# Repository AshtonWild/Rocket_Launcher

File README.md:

# Rocket Launcher

Open hardware for a hobby model-rocket system built around two ESP32 boards:

| Board | What it does | Size | Version |
|---|---|---|---|
| [Rocket V1 flight computer](docs/rocket-v1.md) | Flies in the rocket. Drives four canard servos, reads an IMU and logs to microSD. | 70 × 50 mm, 2 layers | V1 |
| [Ground Station V1 launch controller](docs/ground-station-v1.md) | Stays at the pad. Arms and fires the igniter, checks continuity, and reads GPS, compass and barometer. | 100 × 70 mm, 2 layers | V1 |

Both boards are through-hole only, so they can be hand-soldered, and both use a socketed 30-pin ESP32 DevKit V1. They talk to each other before launch over a 3-wire serial umbilical.

Designed by **Ashton W** in KiCad 10.

| Rocket V1 | Ground Station V1 |
|---|---|
|  |  |

## Safety

The Ground Station switches a 12 V battery into a pyrotechnic igniter. Treat it as live whenever the igniter battery is connected.

- Fit the **SAFE shunt** (J6) whenever you are near the rocket. It shorts the igniter leads together.
- Pull the **ARM plug** (J3) and remove the **key** before approaching the pad.
- The red **ARMED** LED is wired directly to the armed 12 V line. If it is lit, the firing circuit has power, whatever the ESP32 is doing.
- The continuity check passes about 13 µA through the igniter. With the SAFE shunt fitted it reads "connected" whether or not an igniter is attached.
- Follow your national model-rocketry safety code and local law. This design is provided as-is, with no warranty; you are responsible for how you build and use it.

## Documentation

| Document | What it covers |
|---|---|
| [User manual](docs/user-manual.md) | Assembly, bench tests, installation and the launch-day procedure |
| [How it works](docs/how-it-works.md) | Circuit-by-circuit technical description of both boards |
| [Rocket V1](docs/rocket-v1.md) | Connectors, ESP32 pins, test points and known issues |
| [Ground Station V1](docs/ground-station-v1.md) | Firing circuit, connectors, ESP32 pins and known issues |
| [Manufacturing](docs/manufacturing.md) | Ordering the boards from JLCPCB |
| [Changelog](CHANGELOG.md) | What is in this release |

## Repository layout

```
Rocket_V1/           KiCad project: flight computer
Ground_Station_V1/   KiCad project: launch controller
lib/                 Shared ESP32 DevKit symbol and footprint
docs/                Board documentation, schematic PDFs, board renders
  rocket-v1.md
  ground-station-v1.md
  user-manual.md
  how-it-works.md
  manufacturing.md
  schematics/        Schematic PDF and SVG for each board
  images/            Board renders and a prototype photo
*/JLCPCB/            Ready-to-order Gerber zip and parts list for each board
CHANGELOG.md         What is in this release
```

## Opening the projects

1. Install [KiCad 10](https://www.kicad.org/download/) or newer.
2. Open `Rocket_V1/Rocket_V1.kicad_pro` or `Ground_Station_V1/Ground_Station_V1.kicad_pro`.

The ESP32 DevKit symbol and footprint load from `lib/` through a relative path, so the folders must stay side by side as they are here. Every other part comes from KiCad's standard libraries.

Don't want to install KiCad? The schematics are in [docs/schematics](docs/schematics) as PDFs.

## Ordering boards

Each project has a `JLCPCB` folder holding a Gerber zip you can upload as-is, the individual Gerber files, and a parts list. Settings and pre-order checks are in [docs/manufacturing.md](docs/manufacturing.md).

## Status

Both boards pass KiCad's electrical and design rule checks with no errors. **Neither revision has been manufactured or tested yet.** Read the "Known issues" section of each board's page before ordering.

Firmware is not part of this repository. Each board page lists the ESP32 pin assignments needed to write it.

## License

Designed by Ashton W. No license has been chosen yet, so all rights are reserved by default. Add a `LICENSE` file before inviting others to reuse the design. CERN-OHL-P and CC BY-SA are common choices for open hardware.

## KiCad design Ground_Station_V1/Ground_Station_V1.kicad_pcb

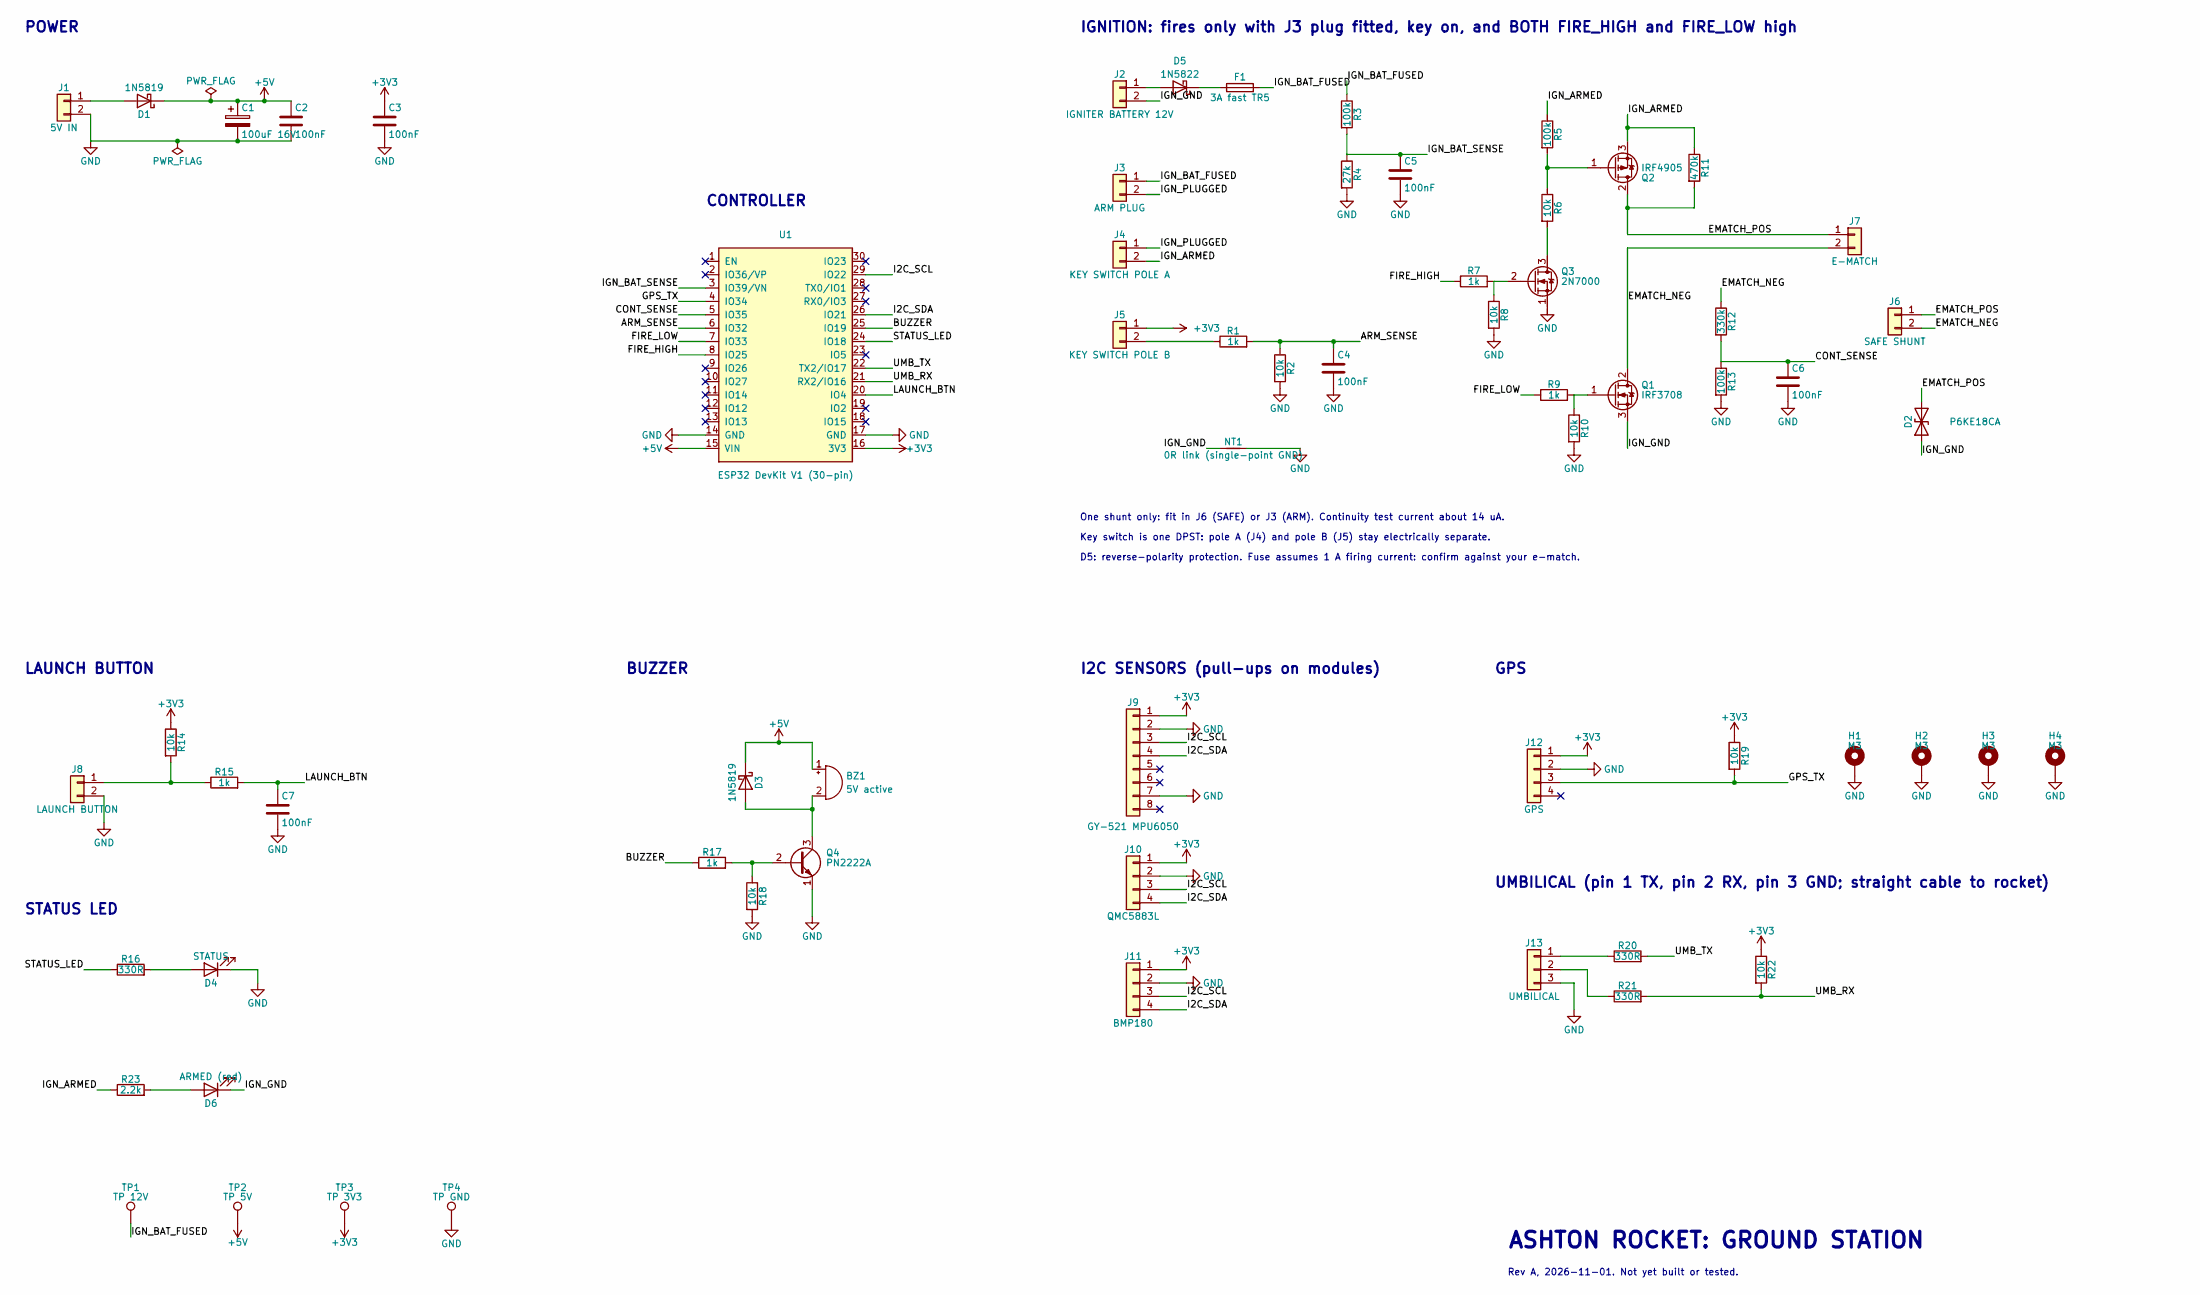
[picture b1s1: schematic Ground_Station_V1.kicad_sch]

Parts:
BZ1: 5V active; Buzzer_12x9.5RM7.6
C1: 100uF 16V; CP_Radial_D6.3mm_P2.50mm
C2, C3, C4, C5, C6, C7: 100nF; C_Disc_D3.0mm_W2.0mm_P2.50mm
D1, D3: 1N5819; D_DO-41_SOD81_P7.62mm_Horizontal
D2: P6KE18CA; D_DO-15_P10.16mm_Horizontal
D4: STATUS; LED_D3.0mm
D5: 1N5822; D_DO-201AD_P12.70mm_Horizontal
D6: ARMED (red); LED_D3.0mm
F1: 3A fast TR5; Fuse_Littelfuse_372_D8.50mm
H1, H2, H3, H4: M3; MountingHole_3.2mm_M3_DIN965_Pad
J1: 5V IN; TerminalBlock_Phoenix_MKDS-1,5-2-5.08_1x02_P5.08mm_Horizont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
J2: IGNITER BATTERY 12V; TerminalBlock_Phoenix_MKDS-1,5-2-5.08_1x02_P5.08mm_Horizont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
J3: ARM PLUG; PinHeader_1x02_P2.54mm_Vertical
J4: KEY SWITCH POLE A; TerminalBlock_Phoenix_MKDS-1,5-2-5.08_1x02_P5.08mm_Horizont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
J5: KEY SWITCH POLE B; PinHeader_1x02_P2.54mm_Vertical
J6: SAFE SHUNT; PinHeader_1x02_P2.54mm_Vertical
J7: E-MATCH; TerminalBlock_Phoenix_MKDS-1,5-2-5.08_1x02_P5.08mm_Horizont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
J8: LAUNCH BUTTON; PinHeader_1x02_P2.54mm_Vertical
J9: GY-521 MPU6050; PinHeader_1x08_P2.54mm_Vertical
J10: QMC5883L; PinHeader_1x04_P2.54mm_Vertical
J11: BMP180; PinHeader_1x04_P2.54mm_Vertical
J12: GPS; PinHeader_1x04_P2.54mm_Vertical
J13: UMBILICAL; PinHeader_1x03_P2.54mm_Vertical
NT1: 0R link (single-point GND); R_Axial_DIN0207_L6.3mm_D2.5mm_P7.62mm_Horizontal
Q1: IRF3708; TO-220-3_Vertical
Q2: IRF4905; TO-220-3_Vertical
Q3: 2N7000; TO-92_Inline
Q4: PN2222A; TO-92_Inline
R1, R7, R9, R15, R17: 1k; R_Axial_DIN0207_L6.3mm_D2.5mm_P7.62mm_Horizontal
R2, R6, R8, R10, R14, R18, R19, R22: 10k; R_Axial_DIN0207_L6.3mm_D2.5mm_P7.62mm_Horizontal
R3, R5, R13: 100k; R_Axial_DIN0207_L6.3mm_D2.5mm_P7.62mm_Horizontal
R4: 27k; R_Axial_DIN0207_L6.3mm_D2.5mm_P7.62mm_Horizontal
R11: 470k; R_Axial_DIN0207_L6.3mm_D2.5mm_P7.62mm_Horizontal
R12: 330k; R_Axial_DIN0207_L6.3mm_D2.5mm_P7.62mm_Horizontal
R16, R20, R21: 330R; R_Axial_DIN0207_L6.3mm_D2.5mm_P7.62mm_Horizontal
R23: 2.2k; R_Axial_DIN0207_L6.3mm_D2.5mm_P7.62mm_Horizontal
TP1: TP 12V; TestPoint_Keystone_5000-5004_Miniature
TP2: TP 5V; TestPoint_Keystone_5000-5004_Miniature
TP3: TP 3V3; TestPoint_Keystone_5000-5004_Miniature
TP4: TP GND; TestPoint_Keystone_5000-5004_Miniature
U1: ESP32 DevKit V1 (30-pin); ESP32_DevKit_V1_30pin_Socket

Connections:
+3V3: C3.1, J5.1, J9.1, J10.1, J11.1, J12.1, R14.1, R19.1, R22.1, TP3.1, U1.16 (3V3)
+5V: BZ1.1 (+), C1.1, C2.1, D1.1 (K), D3.1 (K), TP2.1, U1.15 (VIN)
/ARM_SENSE: C4.1, R1.2, R2.1, U1.6 (IO32)
/BUZZER: R17.1, U1.25 (IO19)
/CONT_SENSE: C6.1, R12.2, R13.1, U1.5 (IO35)
/EMATCH_NEG: J6.2, J7.2, Q1.2 (D), R12.1
/EMATCH_POS: D2.2 (A2), J6.1, J7.1, Q2.2 (D), R11.2
/FIRE_HIGH: R7.1, U1.8 (IO25)
/FIRE_LOW: R9.1, U1.7 (IO33)
/GPS_TX: J12.3, R19.2, U1.4 (IO34)
/I2C_SCL: J9.3, J10.3, J11.3, U1.29 (IO22)
/I2C_SDA: J9.4, J10.4, J11.4, U1.26 (IO21)
/IGN_ARMED: J4.2, Q2.3 (S), R5.1, R11.1, R23.1
/IGN_BAT_FUSED: F1.2, J3.1, R3.1, TP1.1
/IGN_BAT_SENSE: C5.1, R3.2, R4.1, U1.3 (IO39/VN)
/IGN_GND: D2.1 (A1), D6.1 (K), J2.2, NT1.1, Q1.3 (S)
/IGN_PLUGGED: J3.2, J4.1
/LAUNCH_BTN: C7.1, R15.2, U1.20 (IO4)
/STATUS_LED: R16.1, U1.24 (IO18)
/UMB_RX: R21.2, R22.2, U1.21 (RX2/IO16)
/UMB_TX: R20.2, U1.22 (TX2/IO17)
GND: C1.2, C2.2, C3.2, C4.2, C5.2, C6.2, C7.2, D4.1 (K), H1.1, H2.1, H3.1, H4.1, J1.2, J8.2, J9.2, J9.7, J10.2, J11.2, J12.2, J13.3, NT1.2, Q3.1 (S), Q4.1 (E), R2.2, R4.2, R8.2, R10.2, R13.2, R18.2, TP4.1, U1.14 (GND), U1.17 (GND)
unnamed: BZ1.2 (-), D3.2 (A), Q4.3 (C)
unnamed: D1.2 (A), J1.1
unnamed: D4.2 (A), R16.2
unnamed: D5.2 (A), J2.1
unnamed: D5.1 (K), F1.1
unnamed: D6.2 (A), R23.2
unnamed: J5.2, R1.1
unnamed: J8.1, R14.2, R15.1
unnamed: J13.1, R20.1
unnamed: J13.2, R21.1
unnamed: Q1.1 (G), R9.2, R10.1
unnamed: Q2.1 (G), R5.2, R6.1
unnamed: Q3.3 (D), R6.2
unnamed: Q3.2 (G), R7.2, R8.1
unnamed: Q4.2 (B), R17.2, R18.1

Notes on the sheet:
POWER
CONTROLLER
IGNITION: fires only with J3 plug fitted, key on, and BOTH FIRE_HIGH and FIRE_LOW high
LAUNCH BUTTON
STATUS LED
BUZZER
I2C SENSORS (pull-ups on modules)
GPS
UMBILICAL (pin 1 TX, pin 2 RX, pin 3 GND; straight cable to rocket)
One shunt only: fit in J6 (SAFE) or J3 (ARM). Continuity test current about 14 uA.
Key switch is one DPST: pole A (J4) and pole B (J5) stay electrically separate.
ASHTON ROCKET: GROUND STATION
Rev A, 2026-11-01. Not yet built or tested.
D5: reverse-polarity protection. Fuse assumes 1 A firing current: confirm against your e-match.

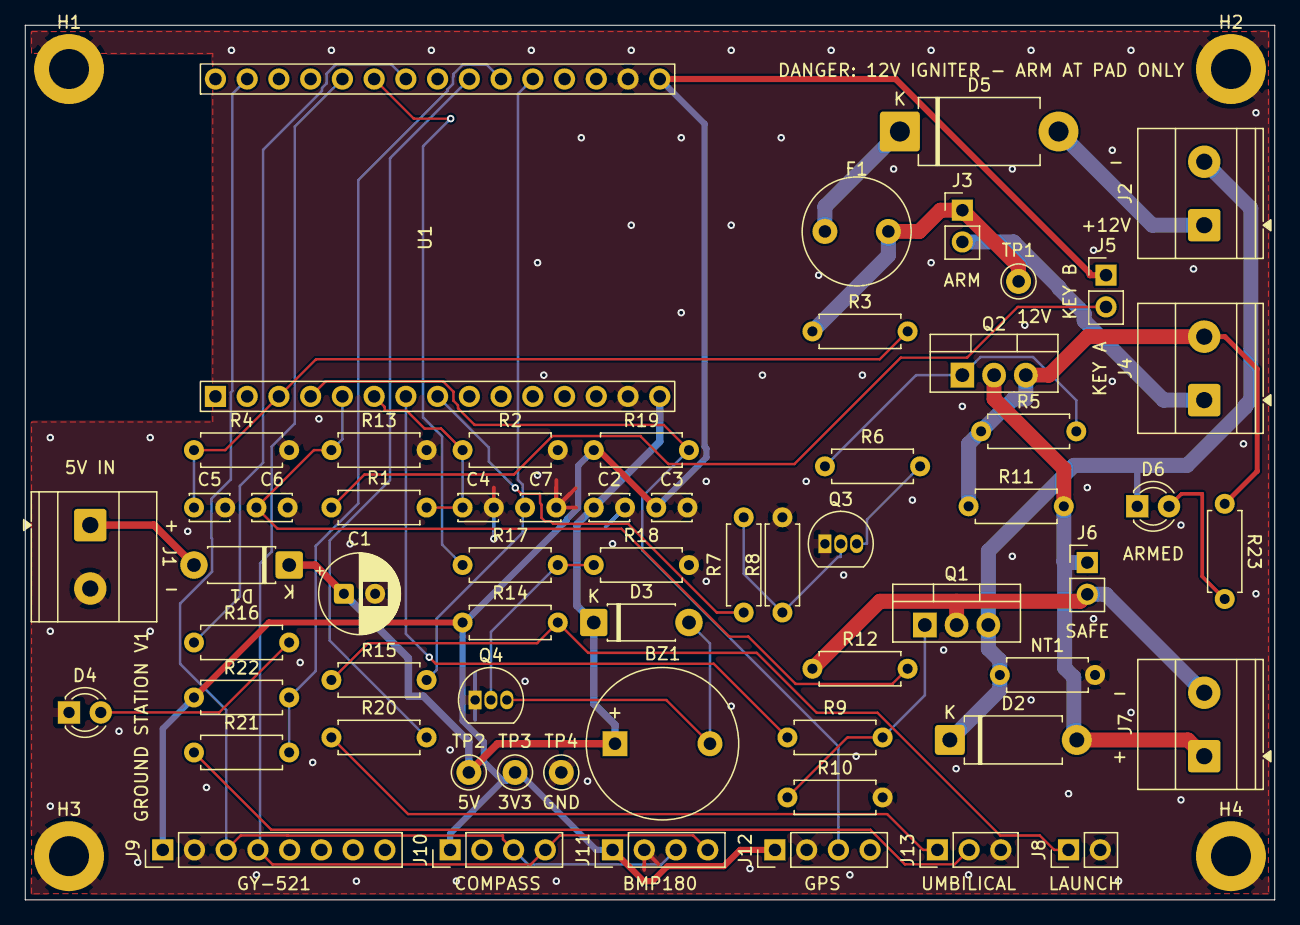
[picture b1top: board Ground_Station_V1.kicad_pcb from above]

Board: 2 copper layers, 100.0 x 70.0 mm, 65 parts (0 on the bottom side), 37 nets.

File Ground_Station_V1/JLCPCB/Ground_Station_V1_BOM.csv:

"Reference","Value","Footprint","QUANTITY"
"BZ1","5V active","Buzzer_Beeper:Buzzer_12x9.5RM7.6","1"
"C1","100uF 16V","Capacitor_THT:CP_Radial_D6.3mm_P2.50mm","1"
"C2-C7","100nF","Capacitor_THT:C_Disc_D3.0mm_W2.0mm_P2.50mm","6"
"D1,D3","1N5819","Diode_THT:D_DO-41_SOD81_P7.62mm_Horizontal","2"
"D2","P6KE18CA","Diode_THT:D_DO-15_P10.16mm_Horizontal","1"
"D4","STATUS","LED_THT:LED_D3.0mm","1"
"D5","1N5822","Diode_THT:D_DO-201AD_P12.70mm_Horizontal","1"
"D6","ARMED (red)","LED_THT:LED_D3.0mm","1"
"F1","3A fast TR5","Fuse:Fuse_Littelfuse_372_D8.50mm","1"
"H1-H4","M3","MountingHole:MountingHole_3.2mm_M3_DIN965_Pad","4"
"J1","5V IN","TerminalBlock_Phoenix:TerminalBlock_Phoenix_MKDS-1,5-2-5.08_1x02_P5.08mm_Horizontal","1"
"J2","IGNITER BATTERY 12V","TerminalBlock_Phoenix:TerminalBlock_Phoenix_MKDS-1,5-2-5.08_1x02_P5.08mm_Horizontal","1"
"J3","ARM PLUG","Connector_PinHeader_2.54mm:PinHeader_1x02_P2.54mm_Vertical","1"
"J4","KEY SWITCH POLE A","TerminalBlock_Phoenix:TerminalBlock_Phoenix_MKDS-1,5-2-5.08_1x02_P5.08mm_Horizontal","1"
"J5","KEY SWITCH POLE B","Connector_PinHeader_2.54mm:PinHeader_1x02_P2.54mm_Vertical","1"
"J6","SAFE SHUNT","Connector_PinHeader_2.54mm:PinHeader_1x02_P2.54mm_Vertical","1"
"J7","E-MATCH","TerminalBlock_Phoenix:TerminalBlock_Phoenix_MKDS-1,5-2-5.08_1x02_P5.08mm_Horizontal","1"
"J8","LAUNCH BUTTON","Connector_PinHeader_2.54mm:PinHeader_1x02_P2.54mm_Vertical","1"
"J9","GY-521 MPU6050","Connector_PinHeader_2.54mm:PinHeader_1x08_P2.54mm_Vertical","1"
"J10","QMC5883L","Connector_PinHeader_2.54mm:PinHeader_1x04_P2.54mm_Vertical","1"
"J11","BMP180","Connector_PinHeader_2.54mm:PinHeader_1x04_P2.54mm_Vertical","1"
"J12","GPS","Connector_PinHeader_2.54mm:PinHeader_1x04_P2.54mm_Vertical","1"
"J13","UMBILICAL","Connector_PinHeader_2.54mm:PinHeader_1x03_P2.54mm_Vertical","1"
"NT1","0R link (single-point GND)","Resistor_THT:R_Axial_DIN0207_L6.3mm_D2.5mm_P7.62mm_Horizontal","1"
"Q1","IRF3708","Package_TO_SOT_THT:TO-220-3_Vertical","1"
"Q2","IRF4905","Package_TO_SOT_THT:TO-220-3_Vertical","1"
"Q3","2N7000","Package_TO_SOT_THT:TO-92_Inline","1"
"Q4","PN2222A","Package_TO_SOT_THT:TO-92_Inline","1"
"R1,R7,R9,R15,R17","1k","Resistor_THT:R_Axial_DIN0207_L6.3mm_D2.5mm_P7.62mm_Horizontal","5"
"R2,R6,R8,R10,R14,R18,R19,R22","10k","Resistor_THT:R_Axial_DIN0207_L6.3mm_D2.5mm_P7.62mm_Horizontal","8"
"R3,R5,R13","100k","Resistor_THT:R_Axial_DIN0207_L6.3mm_D2.5mm_P7.62mm_Horizontal","3"
"R4","27k","Resistor_THT:R_Axial_DIN0207_L6.3mm_D2.5mm_P7.62mm_Horizontal","1"
"R11","470k","Resistor_THT:R_Axial_DIN0207_L6.3mm_D2.5mm_P7.62mm_Horizontal","1"
"R12","330k","Resistor_THT:R_Axial_DIN0207_L6.3mm_D2.5mm_P7.62mm_Horizontal","1"
"R16,R20,R21","330R","Resistor_THT:R_Axial_DIN0207_L6.3mm_D2.5mm_P7.62mm_Horizontal","3"
"R23","2.2k","Resistor_THT:R_Axial_DIN0207_L6.3mm_D2.5mm_P7.62mm_Horizontal","1"
"TP1","TP 12V","TestPoint:TestPoint_Keystone_5000-5004_Miniature","1"
"TP2","TP 5V","TestPoint:TestPoint_Keystone_5000-5004_Miniature","1"
"TP3","TP 3V3","TestPoint:TestPoint_Keystone_5000-5004_Miniature","1"
"TP4","TP GND","TestPoint:TestPoint_Keystone_5000-5004_Miniature","1"
"U1","ESP32 DevKit V1 (30-pin)","ESP32_DevKit:ESP32_DevKit_V1_30pin_Socket","1"

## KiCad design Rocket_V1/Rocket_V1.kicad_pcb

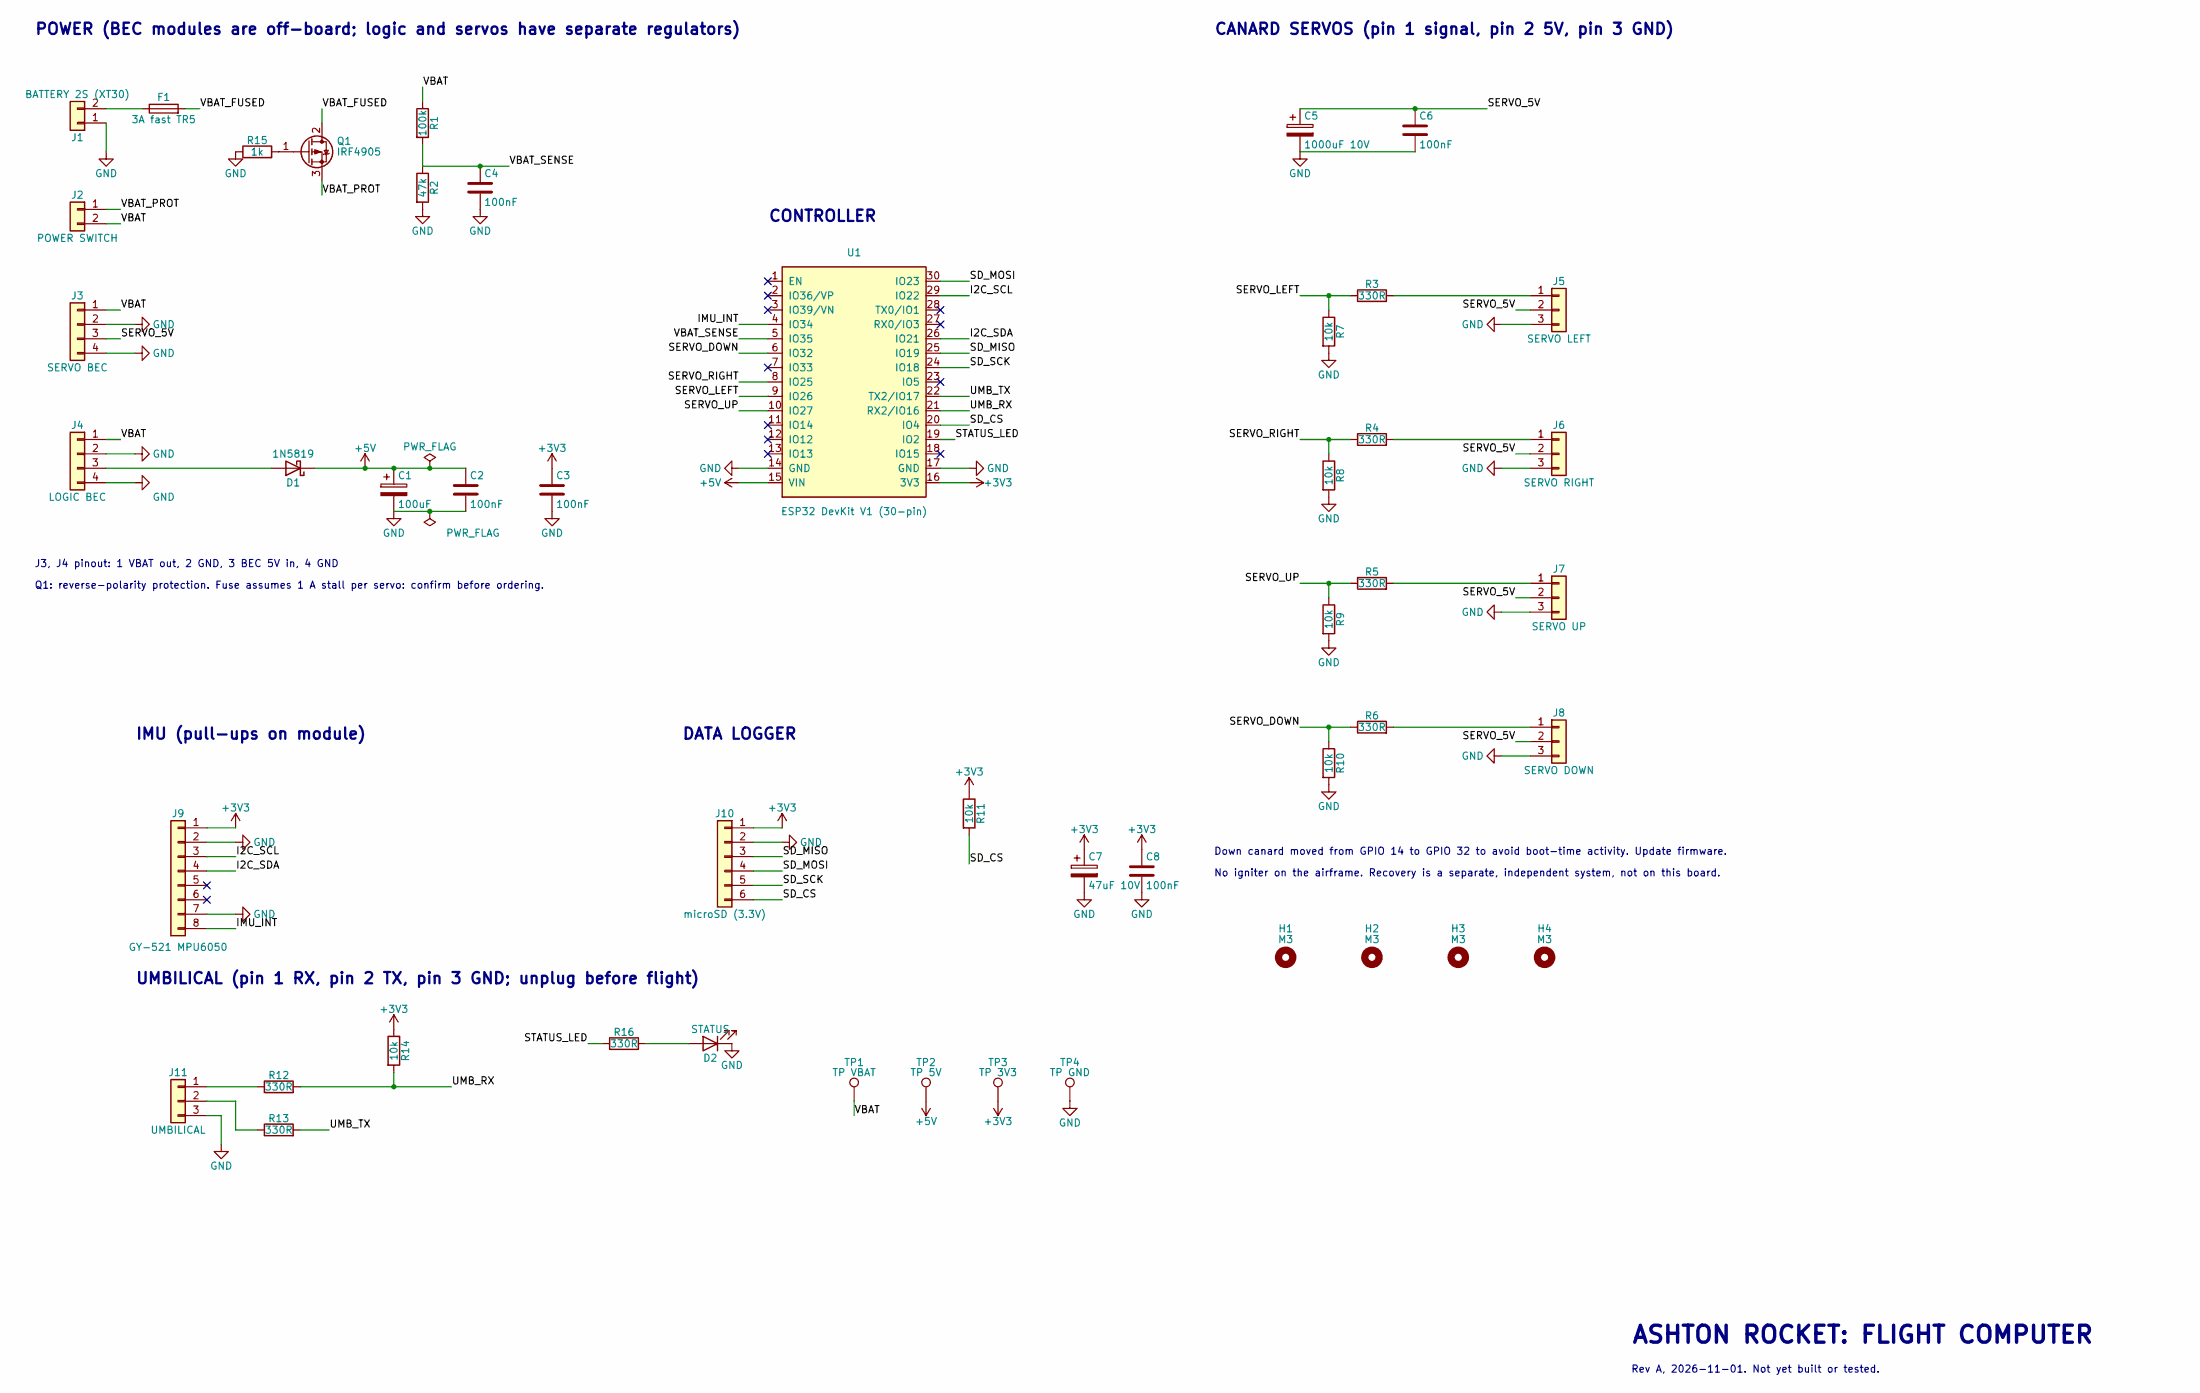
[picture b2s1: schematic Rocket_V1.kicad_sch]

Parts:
C1: 100uF; CP_Radial_D6.3mm_P2.50mm; Voltage 16V
C2, C3, C4, C6, C8: 100nF; C_Disc_D3.0mm_W2.0mm_P2.50mm
C5: 1000uF 10V; CP_Radial_D10.0mm_P5.00mm
C7: 47uF 10V; CP_Radial_D5.0mm_P2.50mm
D1: 1N5819; D_DO-41_SOD81_P7.62mm_Horizontal
D2: STATUS; LED_D3.0mm
F1: 3A fast TR5; Fuse_Littelfuse_372_D8.50mm; Voltage 32V min
H1, H2, H3, H4: M3; MountingHole_3.2mm_M3
J1: BATTERY 2S (XT30); AMASS_XT30U-M_1x02_P5.0mm_Vertical
J2: POWER SWITCH; PinHeader_1x02_P2.54mm_Vertical
J3: SERVO BEC; PinHeader_1x04_P2.54mm_Vertical
J4: LOGIC BEC; PinHeader_1x04_P2.54mm_Vertical
J5: SERVO LEFT; PinHeader_1x03_P2.54mm_Vertical
J6: SERVO RIGHT; PinHeader_1x03_P2.54mm_Vertical
J7: SERVO UP; PinHeader_1x03_P2.54mm_Vertical
J8: SERVO DOWN; PinHeader_1x03_P2.54mm_Vertical
J9: GY-521 MPU6050; PinHeader_1x08_P2.54mm_Vertical
J10: microSD (3.3V); PinHeader_1x06_P2.54mm_Vertical
J11: UMBILICAL; PinHeader_1x03_P2.54mm_Vertical
Q1: IRF4905; TO-220-3_Horizontal_TabUp
R1: 100k; R_Axial_DIN0207_L6.3mm_D2.5mm_P7.62mm_Horizontal
R2: 47k; R_Axial_DIN0207_L6.3mm_D2.5mm_P7.62mm_Horizontal
R3, R4, R5, R6, R12, R13, R16: 330R; R_Axial_DIN0207_L6.3mm_D2.5mm_P7.62mm_Horizontal
R7, R8, R9, R10, R11, R14: 10k; R_Axial_DIN0207_L6.3mm_D2.5mm_P7.62mm_Horizontal
R15: 1k; R_Axial_DIN0207_L6.3mm_D2.5mm_P7.62mm_Horizontal
TP1: TP VBAT; TestPoint_Keystone_5000-5004_Miniature
TP2: TP 5V; TestPoint_Keystone_5000-5004_Miniature
TP3: TP 3V3; TestPoint_Keystone_5000-5004_Miniature
TP4: TP GND; TestPoint_Keystone_5000-5004_Miniature
U1: ESP32 DevKit V1 (30-pin); ESP32_DevKit_V1_30pin_Socket

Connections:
+3V3: C3.1, C7.1, C8.1, J9.1, J10.1, R11.1, R14.1, TP3.1, U1.16 (3V3)
+5V: C1.1, C2.1, D1.1 (K), TP2.1, U1.15 (VIN)
/I2C_SCL: J9.3, U1.29 (IO22)
/I2C_SDA: J9.4, U1.26 (IO21)
/IMU_INT: J9.8, U1.4 (IO34)
/SD_CS: J10.6, R11.2, U1.20 (IO4)
/SD_MISO: J10.3, U1.25 (IO19)
/SD_MOSI: J10.4, U1.30 (IO23)
/SD_SCK: J10.5, U1.24 (IO18)
/SERVO_5V: C5.1, C6.1, J3.3, J5.2, J6.2, J7.2, J8.2
/SERVO_DOWN: R6.1, R10.1, U1.6 (IO32)
/SERVO_LEFT: R3.1, R7.1, U1.9 (IO26)
/SERVO_RIGHT: R4.1, R8.1, U1.8 (IO25)
/SERVO_UP: R5.1, R9.1, U1.10 (IO27)
/STATUS_LED: R16.1, U1.19 (IO2)
/UMB_RX: R12.2, R14.2, U1.21 (RX2/IO16)
/UMB_TX: R13.2, U1.22 (TX2/IO17)
/VBAT: J2.2, J3.1, J4.1, R1.1, TP1.1
/VBAT_FUSED: F1.2, Q1.2 (D)
/VBAT_PROT: J2.1, Q1.3 (S)
/VBAT_SENSE: C4.1, R1.2, R2.1, U1.5 (IO35)
GND: C1.2, C2.2, C3.2, C4.2, C5.2, C6.2, C7.2, C8.2, D2.1 (K), J1.1, J3.2, J3.4, J4.2, J4.4, J5.3, J6.3, J7.3, J8.3, J9.2, J9.7, J10.2, J11.3, R2.2, R7.2, R8.2, R9.2, R10.2, R15.1, TP4.1, U1.14 (GND), U1.17 (GND)
unnamed: D1.2 (A), J4.3
unnamed: D2.2 (A), R16.2
unnamed: F1.1, J1.2
unnamed: J5.1, R3.2
unnamed: J6.1, R4.2
unnamed: J7.1, R5.2
unnamed: J8.1, R6.2
unnamed: J11.1, R12.1
unnamed: J11.2, R13.1
unnamed: Q1.1 (G), R15.2

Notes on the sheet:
POWER (BEC modules are off-board; logic and servos have separate regulators)
J3, J4 pinout: 1 VBAT out, 2 GND, 3 BEC 5V in, 4 GND
CONTROLLER
CANARD SERVOS (pin 1 signal, pin 2 5V, pin 3 GND)
Down canard moved from GPIO 14 to GPIO 32 to avoid boot-time activity. Update firmware.
No igniter on the airframe. Recovery is a separate, independent system, not on this board.
IMU (pull-ups on module)
DATA LOGGER
UMBILICAL (pin 1 RX, pin 2 TX, pin 3 GND; unplug before flight)
ASHTON ROCKET: FLIGHT COMPUTER
Rev A, 2026-11-01. Not yet built or tested.
Q1: reverse-polarity protection. Fuse assumes 1 A stall per servo: confirm before ordering.

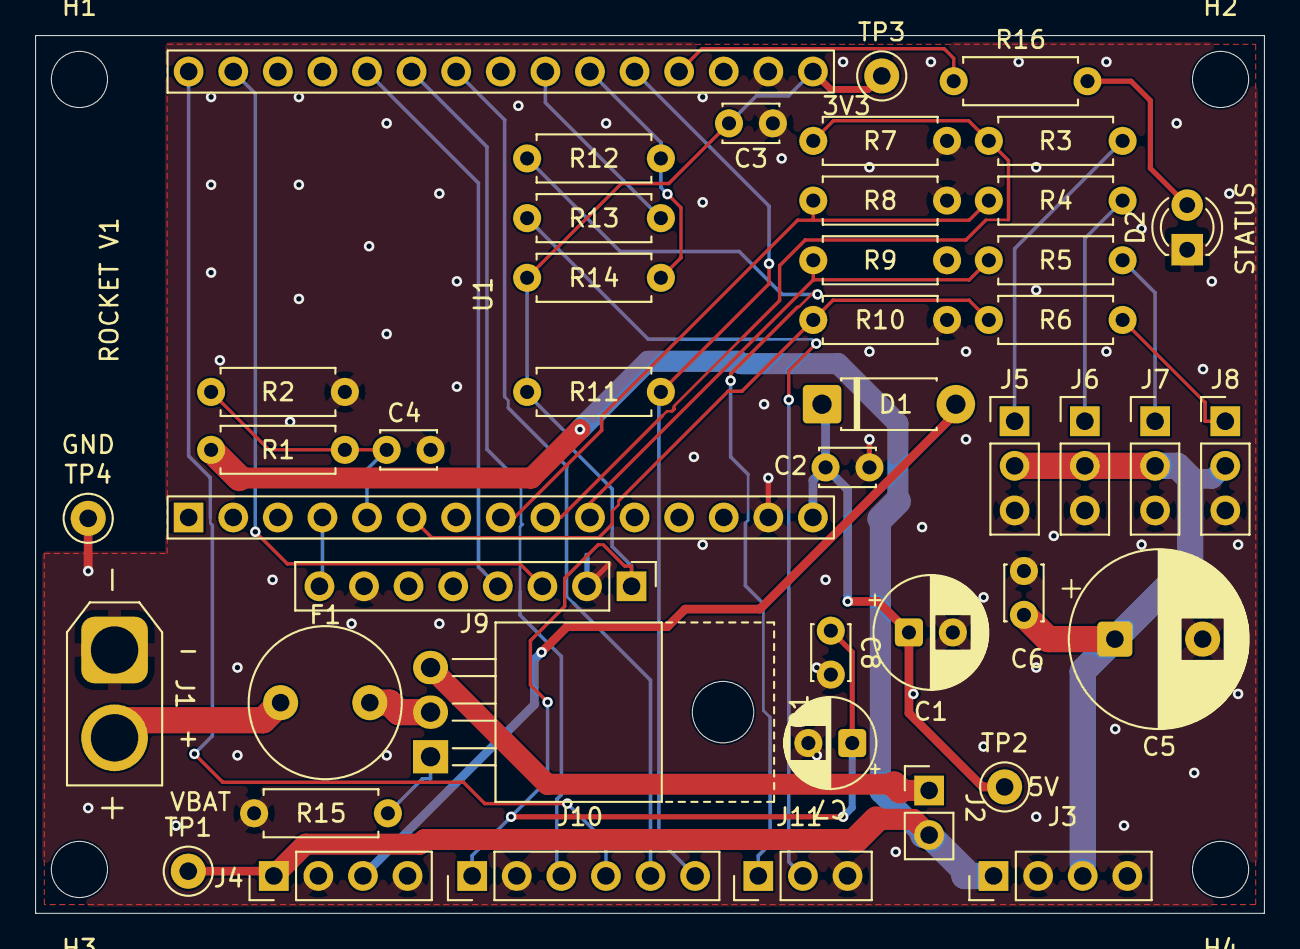
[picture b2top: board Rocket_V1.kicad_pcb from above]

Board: 2 copper layers, 70.0 x 50.0 mm, 48 parts (0 on the bottom side), 32 nets.

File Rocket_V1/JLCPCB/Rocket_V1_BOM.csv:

"Reference","Value","Footprint","QUANTITY"
"C1","100uF","Capacitor_THT:CP_Radial_D6.3mm_P2.50mm","1"
"C2-C4,C6,C8","100nF","Capacitor_THT:C_Disc_D3.0mm_W2.0mm_P2.50mm","5"
"C5","1000uF 10V","Capacitor_THT:CP_Radial_D10.0mm_P5.00mm","1"
"C7","47uF 10V","Capacitor_THT:CP_Radial_D5.0mm_P2.50mm","1"
"D1","1N5819","Diode_THT:D_DO-41_SOD81_P7.62mm_Horizontal","1"
"D2","STATUS","LED_THT:LED_D3.0mm","1"
"F1","3A fast TR5","Fuse:Fuse_Littelfuse_372_D8.50mm","1"
"H1-H4","M3","MountingHole:MountingHole_3.2mm_M3","4"
"J1","BATTERY 2S (XT30)","Connector_AMASS:AMASS_XT30U-M_1x02_P5.0mm_Vertical","1"
"J2","POWER SWITCH","Connector_PinHeader_2.54mm:PinHeader_1x02_P2.54mm_Vertical","1"
"J3","SERVO BEC","Connector_PinHeader_2.54mm:PinHeader_1x04_P2.54mm_Vertical","1"
"J4","LOGIC BEC","Connector_PinHeader_2.54mm:PinHeader_1x04_P2.54mm_Vertical","1"
"J5","SERVO LEFT","Connector_PinHeader_2.54mm:PinHeader_1x03_P2.54mm_Vertical","1"
"J6","SERVO RIGHT","Connector_PinHeader_2.54mm:PinHeader_1x03_P2.54mm_Vertical","1"
"J7","SERVO UP","Connector_PinHeader_2.54mm:PinHeader_1x03_P2.54mm_Vertical","1"
"J8","SERVO DOWN","Connector_PinHeader_2.54mm:PinHeader_1x03_P2.54mm_Vertical","1"
"J9","GY-521 MPU6050","Connector_PinHeader_2.54mm:PinHeader_1x08_P2.54mm_Vertical","1"
"J10","microSD (3.3V)","Connector_PinHeader_2.54mm:PinHeader_1x06_P2.54mm_Vertical","1"
"J11","UMBILICAL","Connector_PinHeader_2.54mm:PinHeader_1x03_P2.54mm_Vertical","1"
"Q1","IRF4905","Package_TO_SOT_THT:TO-220-3_Horizontal_TabUp","1"
"R1","100k","Resistor_THT:R_Axial_DIN0207_L6.3mm_D2.5mm_P7.62mm_Horizontal","1"
"R2","47k","Resistor_THT:R_Axial_DIN0207_L6.3mm_D2.5mm_P7.62mm_Horizontal","1"
"R3-R6,R12,R13,R16","330R","Resistor_THT:R_Axial_DIN0207_L6.3mm_D2.5mm_P7.62mm_Horizontal","7"
"R7-R11,R14","10k","Resistor_THT:R_Axial_DIN0207_L6.3mm_D2.5mm_P7.62mm_Horizontal","6"
"R15","1k","Resistor_THT:R_Axial_DIN0207_L6.3mm_D2.5mm_P7.62mm_Horizontal","1"
"TP1","TP VBAT","TestPoint:TestPoint_Keystone_5000-5004_Miniature","1"
"TP2","TP 5V","TestPoint:TestPoint_Keystone_5000-5004_Miniature","1"
"TP3","TP 3V3","TestPoint:TestPoint_Keystone_5000-5004_Miniature","1"
"TP4","TP GND","TestPoint:TestPoint_Keystone_5000-5004_Miniature","1"
"U1","ESP32 DevKit V1 (30-pin)","ESP32_DevKit:ESP32_DevKit_V1_30pin_Socket","1"
